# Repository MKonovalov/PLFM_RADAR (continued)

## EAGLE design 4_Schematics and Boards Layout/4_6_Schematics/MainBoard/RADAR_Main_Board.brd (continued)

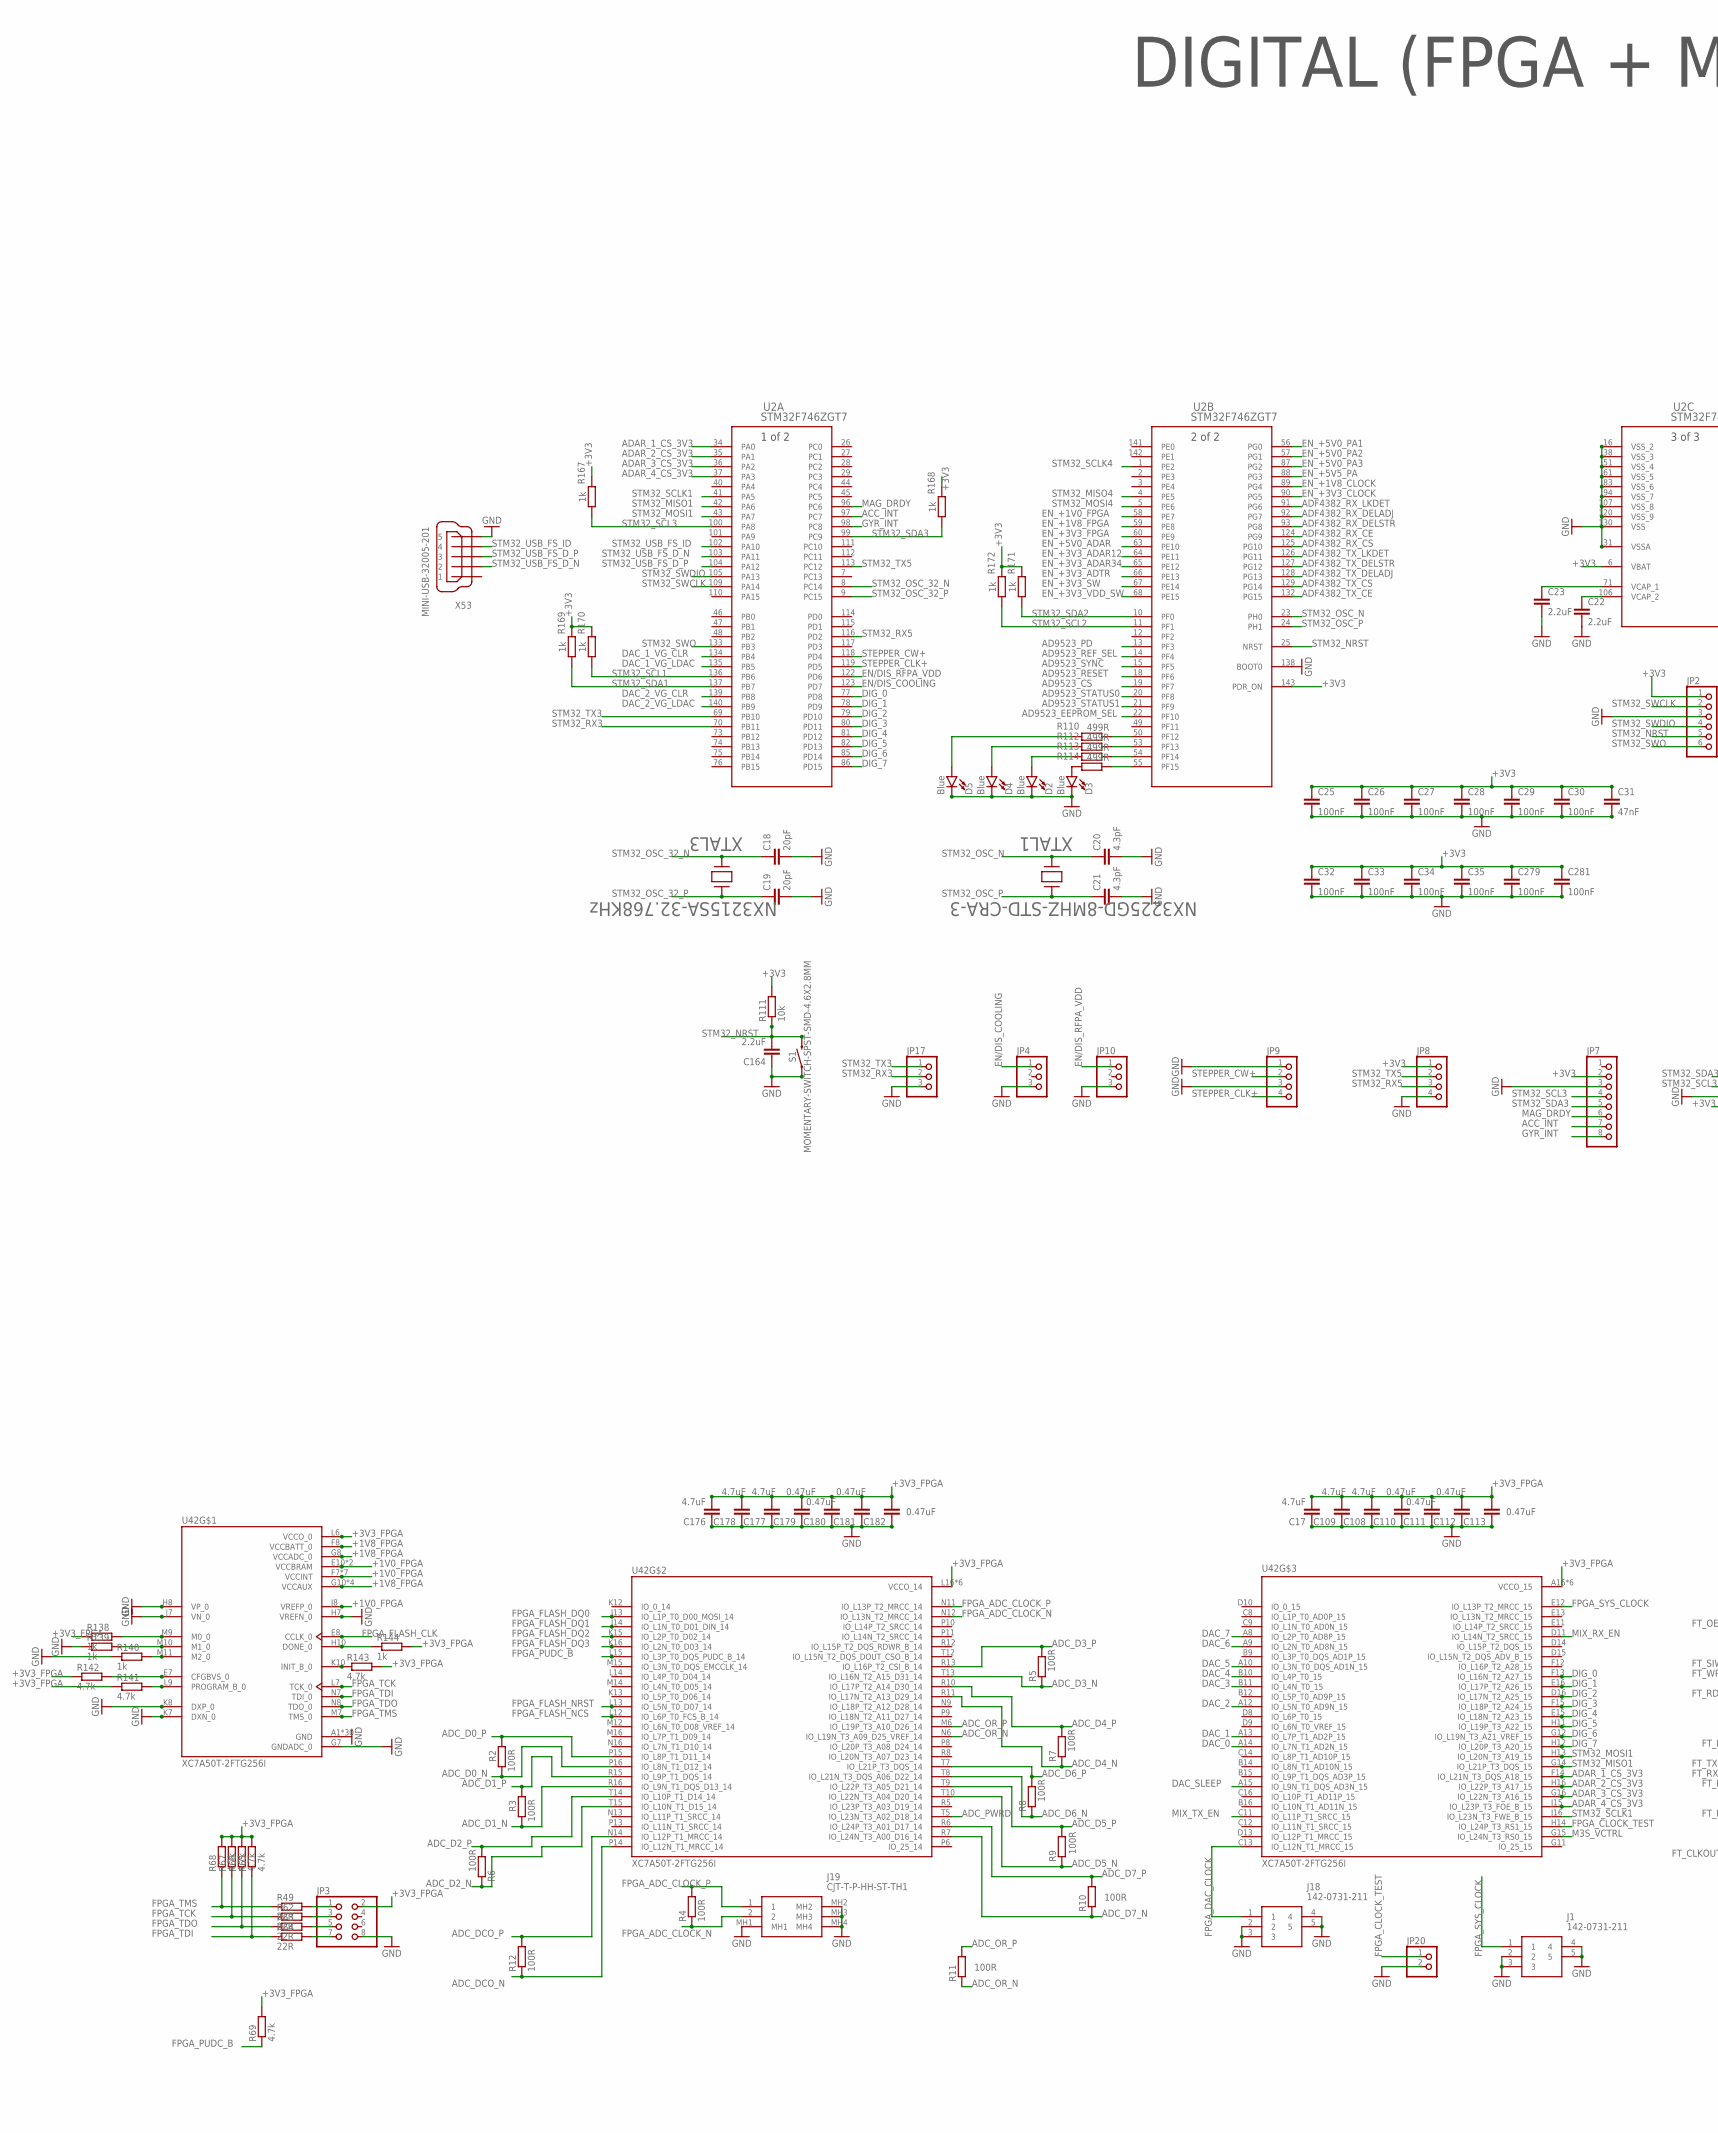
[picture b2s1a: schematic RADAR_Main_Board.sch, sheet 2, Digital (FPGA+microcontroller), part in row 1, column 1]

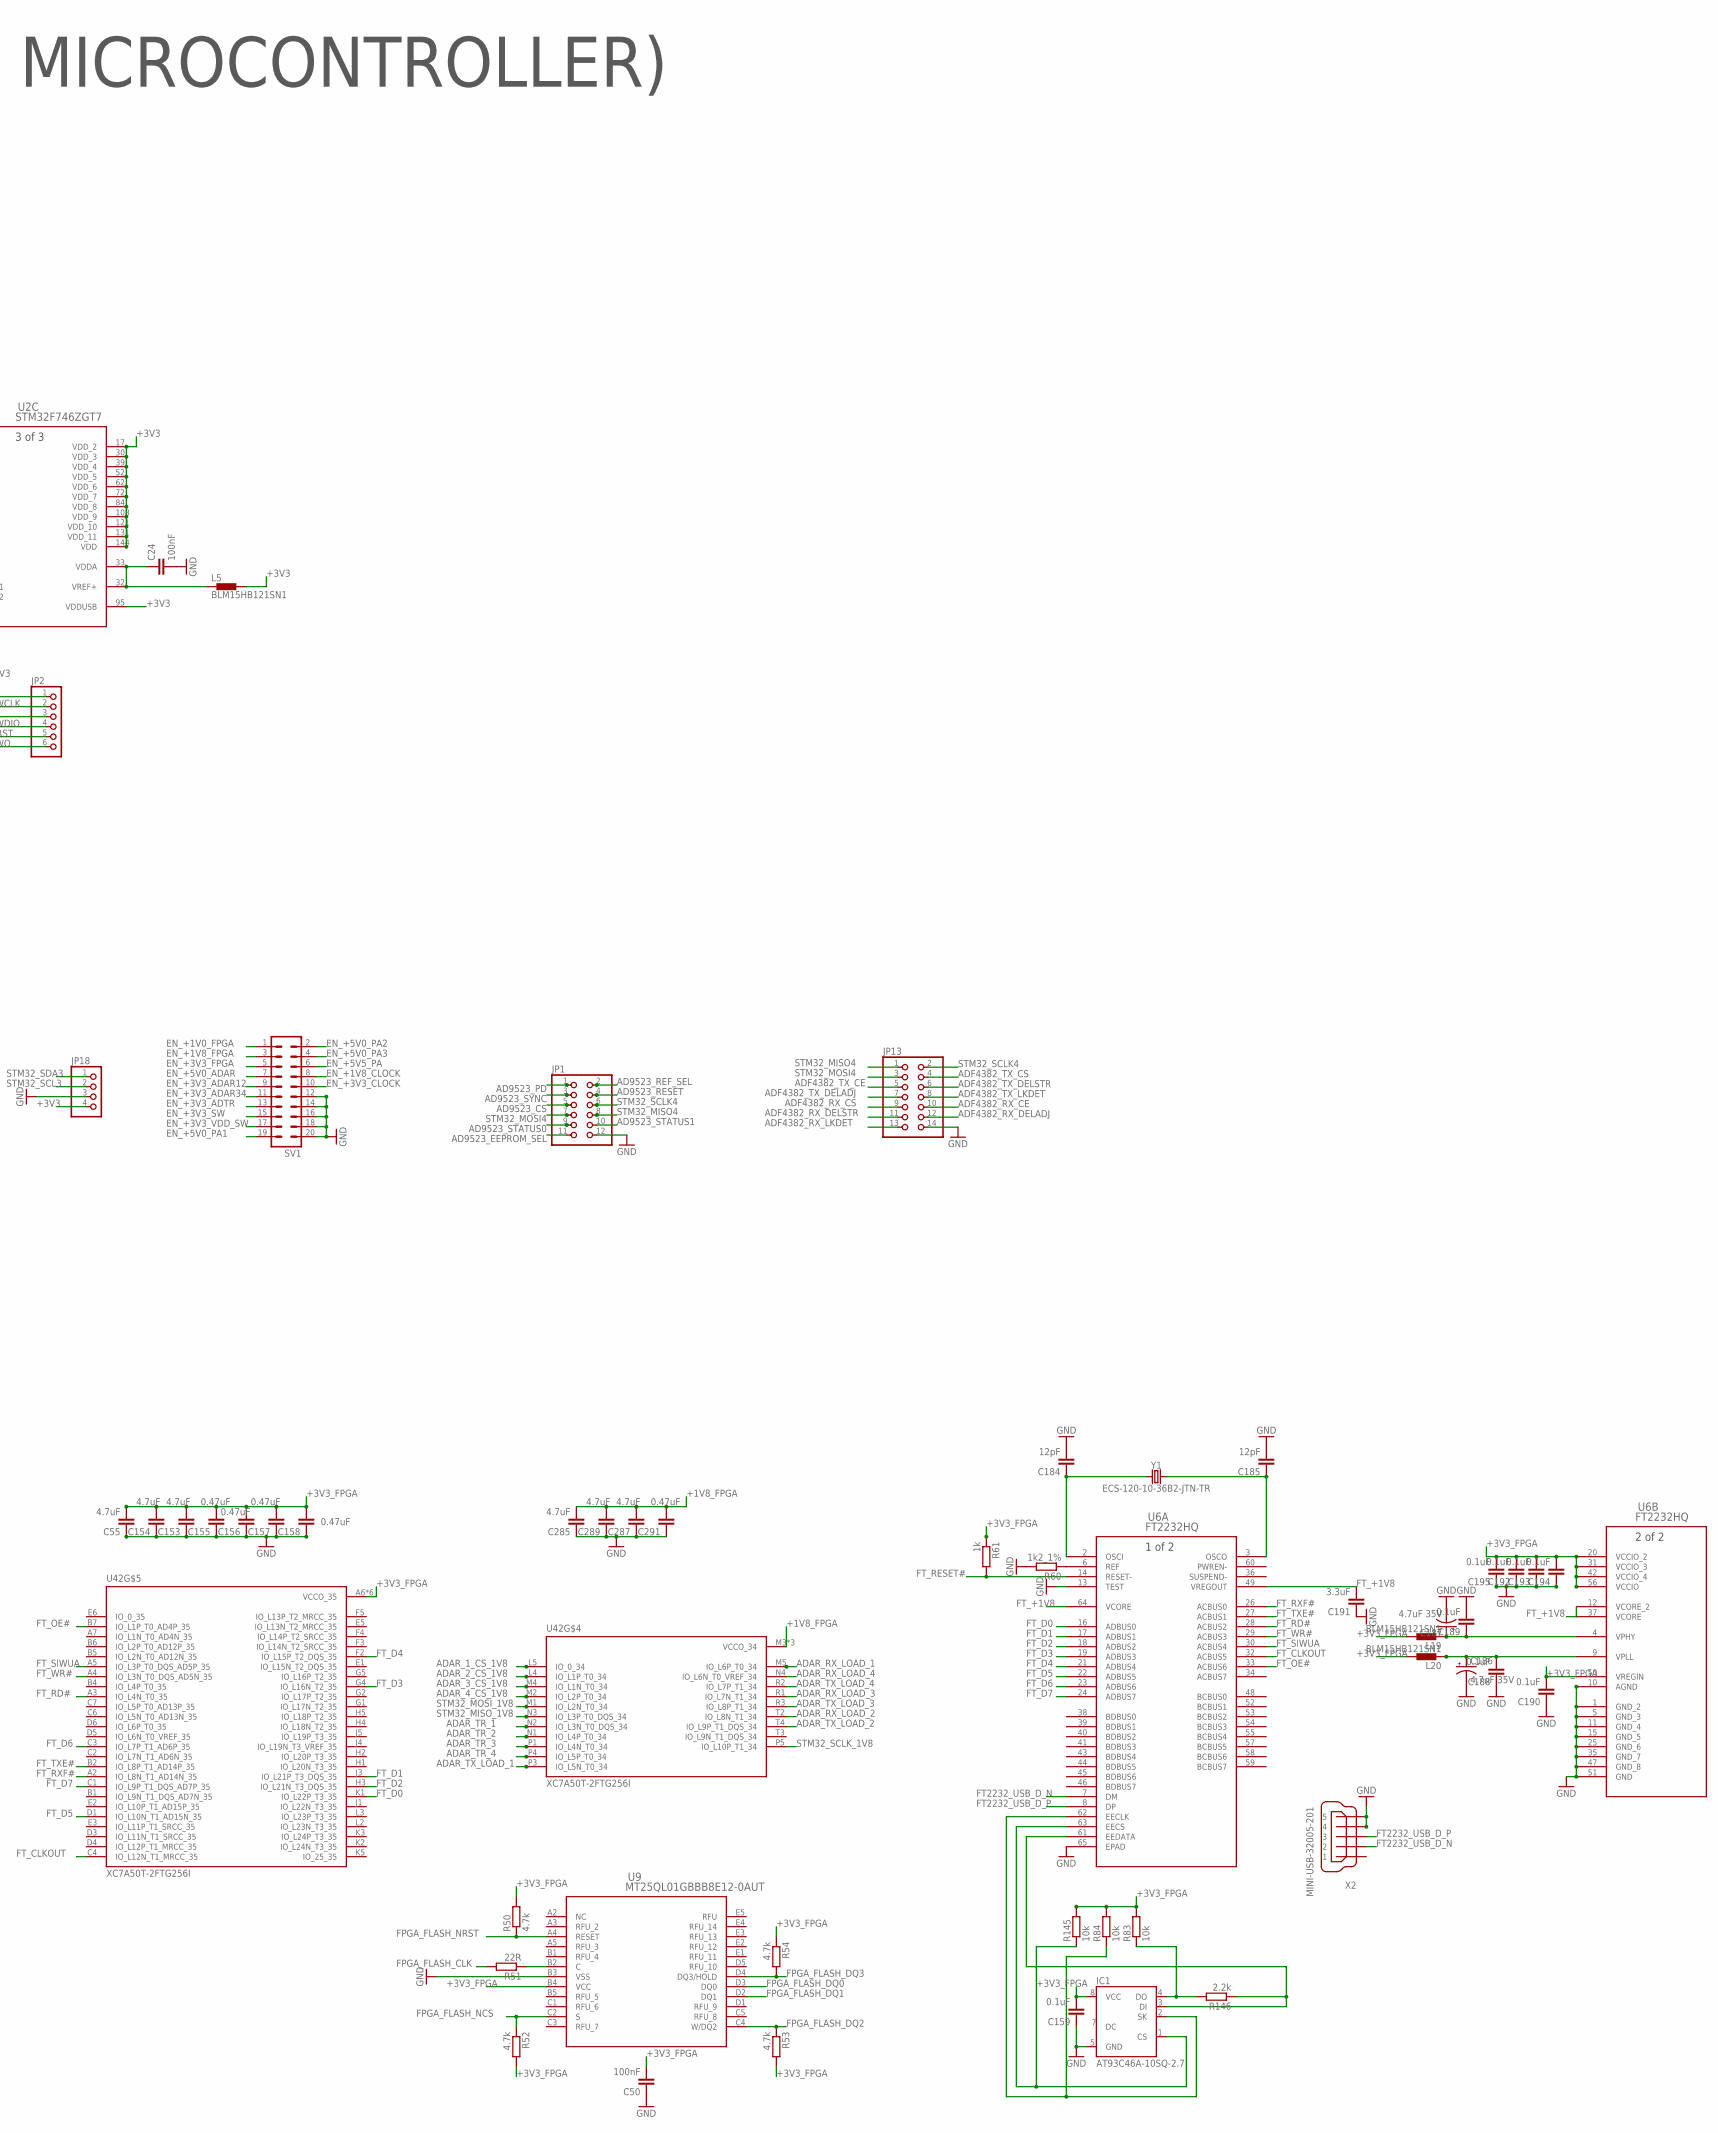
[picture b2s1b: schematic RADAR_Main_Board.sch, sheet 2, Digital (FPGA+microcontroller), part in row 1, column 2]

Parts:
C17, C55, C108, C109, C153, C154, C176, C177, C178, C285, C287, C289: 4.7uF; C0201
C18, C19: 20pF; C0201
C20, C21: 4.3pF; C0201
C22, C23, C164: 2.2uF; C0201
C24, C25, C26, C27, C28, C29, C30, C32, C33, C34, C35, C50, C279, C281: 100nF; C0201
C31: 47nF; C0201
C110, C111, C112, C113, C155, C156, C157, C158, C179, C180, C181, C182, C291: 0.47uF; C0201
C159, C188, C189, C190, C192, C193, C194, C195: 0.1uF; C0201
C184, C185: 12pF; C0201
C186, C187: 4.7uF 35V; EIA3528
C191: 3.3uF; C0201
D2, D3, D4, D5: Blue; LED-0603
IC1: AT93C46A-10SQ-2.7; SOIC8
J1, J18: 142-0731-211; 1420731211
J19: CJT-T-P-HH-ST-TH1; CJTTPHHSTTH1
JP1: PINHD-2X6; 2X06
JP2: PINHD-1X6; 1X06
JP3: PINHD-2X4; 2X04
JP4, JP10, JP17: PINHD-1X3; 1X03
JP7: PINHD-1X8; 1X08
JP8, JP9, JP18: PINHD-1X4; 1X04
JP13: PINHD-2X7; 2X07
JP20: PINHD-1X2; 1X02
L5, L19, L20: BLM15HB121SN1; 0402
R2, R3, R4, R5, R6, R7, R8, R9, R10, R11, R12: 100R; R0201
R49, R51, R62, R63, R64: 22R; R0201
R50, R52, R53, R54, R65, R66, R67, R68, R69, R141, R142, R143: 4.7k; R0201
R60: 1k2_1%; R0201
R61, R138, R139, R140, R144, R167, R168, R169, R170, R171, R172: 1k; R0201
R83, R84, R111, R145: 10k; R0201
R110, R112, R113, R114: 499R; R0201
R146: 2.2k; R0201
S1: MOMENTARY-SWITCH-SPST-SMD-4.6X2.8MM; TACTILE_SWITCH_SMD_4.6X2.8MM
SV1: MA10-2
U2: STM32F746ZGT7; LQFP-144_STM
U6: FT2232HQ; 64QFN_FT2232HQ_FTD
U9: MT25QL01GBBB8E12-0AUT; BGA24_MT25QL_MRN
U42: XC7A50T-2FTG256I; BGA256C100P16X16_1700X1700X155
X2, X53: MINI-USB-32005-201; 32005-201
XTAL1: NX3225GD-8MHZ-STD-CRA-3; XTAL_NX3225GD-8MHZ-STD-CRA-3_N
XTAL3: NX3215SA-32.768KHz; XTAL_NX3225GD-8MHZ-STD-CRA-3_N
Y1: ECS-120-10-36B2-JTN-TR; CRYSTAL-SMD-2X2.5MM

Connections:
+1V0_FPGA: U42.E10 (VCCBRAM), U42.F7 (VCCINT), U42.F9 (VCCINT), U42.F11 (VCCBRAM), U42.G6 (VCCINT), U42.H9 (VCCINT), U42.J6 (VCCINT), U42.J8 (VREFP_0), U42.K9 (VCCINT), U42.L8 (VCCINT); also elsewhere on the board
+1V8_FPGA: C285.2, C287.2, C289.2, C291.2, U42.F8 (VCCBATT_0), U42.G8 (VCCADC_0), U42.G10 (VCCAUX), U42.J10 (VCCAUX), U42.K11 (VCCAUX), U42.L10 (VCCAUX), U42.M3 (VCCO_34), U42.R4 (VCCO_34), U42.T1 (VCCO_34); also elsewhere on the board
+3V3: C25.1, C26.1, C27.1, C28.1, C29.1, C30.1, C31.1, C32.1, C33.1, C34.1, C35.1, C279.1, C281.1, JP2.1, JP7.2, JP8.1, JP18.4, L5.2, R111.2, R167.1, R168.1, R169.1, R170.1, R171.1, R172.1, U2.6 (VBAT), U2.17 (VDD_2), U2.30 (VDD_3), U2.39 (VDD_4), U2.52 (VDD_5), U2.62 (VDD_6), U2.72 (VDD_7), U2.84 (VDD_8), U2.95 (VDDUSB), U2.108 (VDD_9), U2.121 (VDD_10), U2.131 (VDD_11), U2.143 (PDR_ON), U2.144 (VDD); also elsewhere on the board
+3V3_FPGA: C17.2, C50.2, C55.2, C108.2, C109.2, C110.2, C111.2, C112.2, C113.2, C153.2, C154.2, C155.2, C156.2, C157.2, C158.2, C159.2, C176.2, C177.2, C178.2, C179.2, C180.2, C181.2, C182.2, C190.2, C192.2, C193.2, C194.2, C195.2, IC1.8 (VCC), JP3.2, L19.2, L20.2, R50.2, R52.2, R53.2, R54.1, R61.1, R65.2, R66.2, R67.2, R68.2, R69.2, R83.2, R84.2, R138.1, R141.1, R142.1, R143.2, R144.2, R145.2, U6.20 (VCCIO_2), U6.31 (VCCIO_3), U6.42 (VCCIO_4), U6.50 (VREGIN), U6.56 (VCCIO), U9.B4 (VCC), U42.A6 (VCCO_35), U42.A16 (VCCO_15), U42.B3 (VCCO_35), U42.B13 (VCCO_15), U42.C10 (VCCO_15), U42.D7 (VCCO_35), U42.E4 (VCCO_35), U42.E14 (VCCO_15), U42.F1 (VCCO_35), U42.H15 (VCCO_15), U42.J2 (VCCO_35), U42.J12 (VCCO_15), U42.L6 (VCCO_0); also elsewhere on the board
ACC_INT: JP7.7, U2.97 (PC7)
AD9523_CS: JP1.5, U2.19 (PF7)
AD9523_EEPROM_SEL: JP1.11, U2.22 (PF10)
AD9523_PD: JP1.1, U2.13 (PF3)
AD9523_REF_SEL: JP1.2, U2.14 (PF4)
AD9523_RESET: JP1.4, U2.18 (PF6)
AD9523_STATUS0: JP1.9, U2.20 (PF8)
AD9523_STATUS1: JP1.10, U2.21 (PF9)
AD9523_SYNC: JP1.3, U2.15 (PF5)
ADAR_1_CS_1V8: U42.L5 (IO_0_34); also elsewhere on the board
ADAR_1_CS_3V3: U2.34 (PA0), U42.F14 (IO_L21N_T3_DQS_A18_15)
ADAR_2_CS_1V8: U42.L4 (IO_L1P_T0_34); also elsewhere on the board
ADAR_2_CS_3V3: U2.35 (PA1), U42.H16 (IO_L22P_T3_A17_15)
ADAR_3_CS_1V8: U42.M4 (IO_L1N_T0_34); also elsewhere on the board
ADAR_3_CS_3V3: U2.36 (PA2), U42.G16 (IO_L22N_T3_A16_15)
ADAR_4_CS_1V8: U42.M2 (IO_L2P_T0_34); also elsewhere on the board
ADAR_4_CS_3V3: U2.37 (PA3), U42.J15 (IO_L23P_T3_FOE_B_15)
ADAR_RX_LOAD_1: U42.M5 (IO_L6P_T0_34); also elsewhere on the board
ADAR_RX_LOAD_2: U42.T2 (IO_L8N_T1_34); also elsewhere on the board
ADAR_RX_LOAD_3: U42.R1 (IO_L7N_T1_34); also elsewhere on the board
ADAR_RX_LOAD_4: U42.N4 (IO_L6N_T0_VREF_34); also elsewhere on the board
ADAR_TR_1: U42.N2 (IO_L3N_T0_DQS_34); also elsewhere on the board
ADAR_TR_2: U42.N1 (IO_L4P_T0_34); also elsewhere on the board
ADAR_TR_3: U42.P1 (IO_L4N_T0_34); also elsewhere on the board
ADAR_TR_4: U42.P4 (IO_L5P_T0_34); also elsewhere on the board
ADAR_TX_LOAD_1: U42.P3 (IO_L5N_T0_34); also elsewhere on the board
ADAR_TX_LOAD_2: U42.T4 (IO_L9P_T1_DQS_34); also elsewhere on the board
ADAR_TX_LOAD_3: U42.R3 (IO_L8P_T1_34); also elsewhere on the board
ADAR_TX_LOAD_4: U42.R2 (IO_L7P_T1_34); also elsewhere on the board
ADC_D0_N: R2.1, U42.P16 (IO_L8N_T1_D12_14); also elsewhere on the board
ADC_D0_P: R2.2, U42.P15 (IO_L8P_T1_D11_14); also elsewhere on the board
ADC_D1_N: R3.1, U42.R16 (IO_L9N_T1_DQS_D13_14); also elsewhere on the board
ADC_D1_P: R3.2, U42.R15 (IO_L9P_T1_DQS_14); also elsewhere on the board
ADC_D2_N: R6.1, U42.T15 (IO_L10N_T1_D15_14); also elsewhere on the board
ADC_D2_P: R6.2, U42.T14 (IO_L10P_T1_D14_14); also elsewhere on the board
ADC_D3_N: R5.1, U42.T13 (IO_L16N_T2_A15_D31_14); also elsewhere on the board
ADC_D3_P: R5.2, U42.R13 (IO_L16P_T2_CSI_B_14); also elsewhere on the board
ADC_D4_N: R7.1, U42.R11 (IO_L17N_T2_A13_D29_14); also elsewhere on the board
ADC_D4_P: R7.2, U42.R10 (IO_L17P_T2_A14_D30_14); also elsewhere on the board
ADC_D5_N: R9.1, U42.T10 (IO_L22N_T3_A04_D20_14); also elsewhere on the board
ADC_D5_P: R9.2, U42.T9 (IO_L22P_T3_A05_D21_14); also elsewhere on the board
ADC_D6_N: R8.1, U42.T8 (IO_L21N_T3_DQS_A06_D22_14); also elsewhere on the board
ADC_D6_P: R8.2, U42.T7 (IO_L21P_T3_DQS_14); also elsewhere on the board
ADC_D7_N: R10.1, U42.R7 (IO_L24N_T3_A00_D16_14); also elsewhere on the board
ADC_D7_P: R10.2, U42.R6 (IO_L24P_T3_A01_D17_14); also elsewhere on the board
ADC_DCO_N: R12.1, U42.P14 (IO_L12N_T1_MRCC_14); also elsewhere on the board
ADC_DCO_P: R12.2, U42.N14 (IO_L12P_T1_MRCC_14); also elsewhere on the board
ADC_OR_N: R11.1, U42.N6 (IO_L19N_T3_A09_D25_VREF_14); also elsewhere on the board
ADC_OR_P: R11.2, U42.M6 (IO_L19P_T3_A10_D26_14); also elsewhere on the board
ADC_PWRD: U42.T5 (IO_L23N_T3_A02_D18_14); also elsewhere on the board
ADF4382_RX_CE: JP13.10, U2.124 (PG9)
ADF4382_RX_CS: JP13.9, U2.125 (PG10)
ADF4382_RX_DELADJ: JP13.12, U2.92 (PG7)
ADF4382_RX_DELSTR: JP13.11, U2.93 (PG8)
ADF4382_RX_LKDET: JP13.13, U2.91 (PG6)
ADF4382_TX_CE: JP13.5, U2.132 (PG15)
ADF4382_TX_CS: JP13.4, U2.129 (PG14)
ADF4382_TX_DELADJ: JP13.7, U2.128 (PG13)
ADF4382_TX_DELSTR: JP13.6, U2.127 (PG12)
ADF4382_TX_LKDET: JP13.8, U2.126 (PG11)
DAC_0: U42.A14 (IO_L7N_T1_AD2N_15); also elsewhere on the board
DAC_1: U42.A13 (IO_L7P_T1_AD2P_15); also elsewhere on the board
DAC_1_VG_CLR: U2.134 (PB4); also elsewhere on the board
DAC_1_VG_LDAC: U2.135 (PB5); also elsewhere on the board
DAC_2: U42.A12 (IO_L5N_T0_AD9N_15); also elsewhere on the board
DAC_2_VG_CLR: U2.139 (PB8); also elsewhere on the board
DAC_2_VG_LDAC: U2.140 (PB9); also elsewhere on the board
DAC_3: U42.B11 (IO_L4N_T0_15); also elsewhere on the board
DAC_4: U42.B10 (IO_L4P_T0_15); also elsewhere on the board
DAC_5: U42.A10 (IO_L3N_T0_DQS_AD1N_15); also elsewhere on the board
DAC_6: U42.A9 (IO_L2N_T0_AD8N_15); also elsewhere on the board
DAC_7: U42.A8 (IO_L2P_T0_AD8P_15); also elsewhere on the board
DAC_SLEEP: U42.A15 (IO_L9N_T1_DQS_AD3N_15); also elsewhere on the board
DIG_0: U2.77 (PD8), U42.F13 (IO_L16N_T2_A27_15)
DIG_1: U2.78 (PD9), U42.E16 (IO_L17P_T2_A26_15)
DIG_2: U2.79 (PD10), U42.D16 (IO_L17N_T2_A25_15)
DIG_3: U2.80 (PD11), U42.F15 (IO_L18P_T2_A24_15)
DIG_4: U2.81 (PD12), U42.E15 (IO_L18N_T2_A23_15)
DIG_5: U2.82 (PD13), U42.H11 (IO_L19P_T3_A22_15)
DIG_6: U2.85 (PD14), U42.G12 (IO_L19N_T3_A21_VREF_15)
DIG_7: U2.86 (PD15), U42.H12 (IO_L20P_T3_A20_15)
EN/DIS_COOLING: JP4.1, U2.123 (PD7)
EN/DIS_RFPA_VDD: JP10.1, U2.122 (PD6)
EN_+1V0_FPGA: SV1.1, U2.58 (PE7)
EN_+1V8_CLOCK: SV1.8, U2.89 (PG4)
EN_+1V8_FPGA: SV1.3, U2.59 (PE8)
EN_+3V3_ADAR12: SV1.9, U2.64 (PE11)
EN_+3V3_ADAR34: SV1.11, U2.65 (PE12)
EN_+3V3_ADTR: SV1.13, U2.66 (PE13)
EN_+3V3_CLOCK: SV1.10, U2.90 (PG5)
EN_+3V3_FPGA: SV1.5, U2.60 (PE9)
EN_+3V3_SW: SV1.15, U2.67 (PE14)
EN_+3V3_VDD_SW: SV1.17, U2.68 (PE15)
EN_+5V0_ADAR: SV1.7, U2.63 (PE10)
EN_+5V0_PA1: SV1.19, U2.56 (PG0)
EN_+5V0_PA2: SV1.2, U2.57 (PG1)
EN_+5V0_PA3: SV1.4, U2.87 (PG2)
EN_+5V5_PA: SV1.6, U2.88 (PG3)
FPGA_ADC_CLOCK_N: J19.2, R4.1, U42.N12 (IO_L13N_T2_MRCC_14)
FPGA_ADC_CLOCK_P: J19.1, R4.2, U42.N11 (IO_L13P_T2_MRCC_14)
FPGA_CLOCK_TEST: JP20.1, U42.H14 (IO_L24P_T3_RS1_15)
FPGA_DAC_CLOCK: J18.1, U42.C13 (IO_L12N_T1_MRCC_15)
FPGA_DONE: R144.1, U2.44 (PC4), U42.H10 (DONE_0)
FPGA_FLASH_CLK: R51.2, U42.E8 (CCLK_0)
FPGA_FLASH_DQ0: U42.J13 (IO_L1P_T0_D00_MOSI_14); also elsewhere on the board
FPGA_FLASH_DQ1: U42.J14 (IO_L1N_T0_D01_DIN_14); also elsewhere on the board
FPGA_FLASH_DQ2: R53.1, U42.K15 (IO_L2P_T0_D02_14); also elsewhere on the board
FPGA_FLASH_DQ3: R54.2, U42.K16 (IO_L2N_T0_D03_14); also elsewhere on the board
FPGA_FLASH_NCS: R52.1, U42.L12 (IO_L6P_T0_FCS_B_14); also elsewhere on the board
FPGA_FLASH_NRST: R50.1, U42.L13 (IO_L5N_T0_D07_14); also elsewhere on the board
FPGA_PUDC_B: R69.1, U42.L15 (IO_L3P_T0_DQS_PUDC_B_14)
FPGA_SYS_CLOCK: J1.1, U42.E12 (IO_L13P_T2_MRCC_15)
FPGA_TCK: R62.1, R67.1, U42.L7 (TCK_0)
FPGA_TDI: R64.1, R65.1, U42.N7 (TDI_0)
FPGA_TDO: R63.1, R66.1, U42.N8 (TDO_0)
FPGA_TMS: R49.1, R68.1, U42.M7 (TMS_0)
FT2232_USB_D_N: U6.7 (DM), X2.2
FT2232_USB_D_P: U6.8 (DP), X2.3
FT_+1V8: C191.2, U6.12 (VCORE_2), U6.37 (VCORE), U6.49 (VREGOUT), U6.64 (VCORE)
FT_CLKOUT: U6.32 (ACBUS5), U42.C4 (IO_L12N_T1_MRCC_35)
FT_D0: U6.16 (ADBUS0), U42.K1 (IO_L22P_T3_35)
FT_D1: U6.17 (ADBUS1), U42.J3 (IO_L21P_T3_DQS_35)
FT_D2: U6.18 (ADBUS2), U42.H3 (IO_L21N_T3_DQS_35)
FT_D3: U6.19 (ADBUS3), U42.G4 (IO_L16N_T2_35)
FT_D4: U6.21 (ADBUS4), U42.F2 (IO_L15P_T2_DQS_35)
FT_D5: U6.22 (ADBUS5), U42.D1 (IO_L10N_T1_AD15N_35)
FT_D6: U6.23 (ADBUS6), U42.C3 (IO_L7P_T1_AD6P_35)
FT_D7: U6.24 (ADBUS7), U42.C1 (IO_L9P_T1_DQS_AD7P_35)
FT_OE#: U6.33 (ACBUS6), U42.B7 (IO_L1P_T0_AD4P_35)
FT_RD#: U6.28 (ACBUS2), U42.A3 (IO_L4N_T0_35)
FT_RESET#: R61.2, U6.14 (RESET-)
FT_RXF#: U6.26 (ACBUS0), U42.A2 (IO_L8N_T1_AD14N_35)
FT_SIWUA: U6.30 (ACBUS4), U42.A5 (IO_L3P_T0_DQS_AD5P_35)
FT_TXE#: U6.27 (ACBUS1), U42.B2 (IO_L8P_T1_AD14P_35)
FT_WR#: U6.29 (ACBUS3), U42.A4 (IO_L3N_T0_DQS_AD5N_35)
GYR_INT: JP7.8, U2.98 (PC8)
M3S_VCTRL: U42.G15 (IO_L24N_T3_RS0_15); also elsewhere on the board
MAG_DRDY: JP7.6, U2.96 (PC6)
MIX_RX_EN: U42.D11 (IO_L14N_T2_SRCC_15); also elsewhere on the board
MIX_TX_EN: U42.C11 (IO_L11P_T1_SRCC_15); also elsewhere on the board
unnamed: C23.1, U2.71 (VCAP_1)
unnamed: C22.1, U2.106 (VCAP_2)
unnamed: C24.1, L5.1, U2.32 (VREF+), U2.33 (VDDA)
unnamed: R51.1, U9.B2 (C)
unnamed: JP3.1, R49.2
unnamed: JP3.3, R62.2
unnamed: JP3.5, R63.2
unnamed: JP3.7, R64.2
unnamed: R110.2, U2.50 (PF12)
unnamed: IC1.4 (DO), R83.1, R146.2
unnamed: R112.2, U2.53 (PF13)
unnamed: D3.A, R114.1
unnamed: R113.2, U2.54 (PF14)
unnamed: R114.2, U2.55 (PF15)
unnamed: D2.A, R113.1
unnamed: D4.A, R112.1
unnamed: D5.A, R110.1
unnamed: R138.2, U42.M9 (M0_0)
unnamed: R139.2, U42.M10 (M1_0)
unnamed: R140.2, U42.M11 (M2_0)
unnamed: R141.2, U42.L9 (PROGRAM_B_0)
unnamed: R142.2, U42.E7 (CFGBVS_0)
unnamed: R143.1, U42.K10 (INIT_B_0)
unnamed: R60.1, U6.6 (REF)
unnamed: C184.1, U6.2 (OSCI), Y1.P1 (1)
unnamed: C185.1, U6.3 (OSCO), Y1.P3 (2)
unnamed: C186.A (+), C188.2, L20.1, U6.9 (VPLL)
unnamed: C187.A (+), C189.1, L19.1, U6.4 (VPHY)
unnamed: IC1.1 (CS), R145.1, U6.63 (EECS)
unnamed: IC1.2 (SK), R84.1, U6.62 (EECLK)
unnamed: IC1.3 (DI), R146.1, U6.61 (EEDATA)
STEPPER_CLK+: JP9.4, U2.119 (PD5)
STEPPER_CW+: JP9.2, U2.118 (PD4)
STM32_MISO1: U2.42 (PA6), U42.G14 (IO_L21P_T3_DQS_15)
STM32_MISO4: JP1.8, JP13.1, U2.4 (PE5)
STM32_MISO_1V8: U42.N3 (IO_L3P_T0_DQS_34); also elsewhere on the board
STM32_MOSI1: U2.43 (PA7), U42.H13 (IO_L20N_T3_A19_15)
STM32_MOSI4: JP1.7, JP13.3, U2.5 (PE6)
STM32_MOSI_1V8: U42.M1 (IO_L2N_T0_34); also elsewhere on the board
STM32_NRST: C164.2, JP2.5, R111.1, S1.3 (2), S1.4 (2), U2.25 (NRST)
STM32_OSC_32_N: C18.1, U2.8 (PC14), XTAL3.2
STM32_OSC_32_P: C19.1, U2.9 (PC15), XTAL3.1
STM32_OSC_N: C20.1, U2.23 (PH0), XTAL1.2
STM32_OSC_P: C21.1, U2.24 (PH1), XTAL1.1
STM32_RX3: JP17.2, U2.70 (PB11)
STM32_RX5: JP8.3, U2.116 (PD2)
STM32_SCL1: R170.2, U2.136 (PB6); also elsewhere on the board
STM32_SCL2: R172.2, U2.11 (PF1); also elsewhere on the board
STM32_SCL3: JP7.4, JP18.2, R167.2, U2.100 (PA8)
STM32_SCLK1: U2.41 (PA5), U42.J16 (IO_L23N_T3_FWE_B_15)
STM32_SCLK4: JP1.6, JP13.2, U2.1 (PE2)
STM32_SCLK_1V8: U42.P5 (IO_L10P_T1_34); also elsewhere on the board
STM32_SDA1: R169.2, U2.137 (PB7); also elsewhere on the board
STM32_SDA2: R171.2, U2.10 (PF0); also elsewhere on the board
STM32_SDA3: JP7.5, JP18.1, R168.2, U2.99 (PC9)
STM32_SWCLK: JP2.2, U2.109 (PA14)
STM32_SWDIO: JP2.4, U2.105 (PA13)
STM32_SWO: JP2.6, U2.133 (PB3)
STM32_TX3: JP17.1, U2.69 (PB10)
STM32_TX5: JP8.2, U2.113 (PC12)
STM32_USB_FS_D_N: U2.103 (PA11), X53.2
STM32_USB_FS_D_P: U2.104 (PA12), X53.3
STM32_USB_FS_ID: U2.102 (PA10), X53.4

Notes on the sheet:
DIGITAL (FPGA + MICROCONTROLLER)

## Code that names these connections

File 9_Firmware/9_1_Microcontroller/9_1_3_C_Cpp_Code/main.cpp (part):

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};

/* ---- rail-good monitoring (RAIL_FAULT.h) -----------------------------------
 * Three regulators report PG on the power board, each on its own connector to PC0/PC1/PC2.
 * The pins are read with internal pull-downs, so an open harness reads LOW and is reported
 * as a fault rather than silently as "good".
 */
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static RailFault_Monitor_t g_rails;

/* ---- strobe acknowledgement (STROBE_ACK.h) ---------------------------------
 * The FPGA answers on PC3: a request clears the line, consumption sets it.  We score each
 * request *before* issuing the next one, because the FPGA clears the line as soon as it sees
 * the new request - checking afterwards would always read low.
 */
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static bool     g_ack_path_ok;

/* The FPGA's configuration status (issue #13).  The main board carries FPGA_DONE from the FPGA's
 * DONE_0/INIT_B_0 to U2.PC4, so the MCU can see a failed or partial configuration - which it
 * could not before, when the pins terminated in pull resistors only. */
static FpgaConfig_t g_fpga_cfg;
static bool         g_fpga_cfg_reported;
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 * The ADC's CSB used to be tied to a rail - which the datasheet names as the way to disable the
 * SPI - SCLK/DFS sat on solder jumper SJ1, and SDIO was unconnected.  The pins are
 * DRVDD-referenced 1.8 V logic (absolute maximum 2.0 V), so they reach the MCU through U92, a
 * TXS0104E translator; PC10 = CSB, PC11 = SCLK, PC13 = SDIO.
 */
static uint8_t g_adc_ovr_config;   /* read back at bring-up: 0x01 on a healthy part */
static bool    g_adc_spi_ok;

static void adc_spi_csb(bool level)  { HAL_GPIO_WritePin(GPIOC, GPIO_PIN_10, level ? GPIO_PIN_SET : GPIO_PIN_RESET); }
static void adc_spi_sclk(bool level) { HAL_GPIO_WritePin(GPIOC, GPIO_PIN_11, level ? GPIO_PIN_SET : GPIO_PIN_RESET); }
static void adc_spi_sdio_out(bool level) { HAL_GPIO_WritePin(GPIOC, GPIO_PIN_13, level ? GPIO_PIN_SET : GPIO_PIN_RESET); }

static void adc_spi_sdio_dir(bool output)
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 *
 * The edges must be counted by an interrupt: one pulse is 1 us high with a
 * 3 us period, all within ~21 us of the frame start, which the per-frame main
 * loop cannot sample.  To enable: configure PD15 (FPGA_DIG7_Pin) as a
 * rising-edge EXTI input and register agcPulseCounter.onEdge() through the
 * project's IRQ layer (no_os_irq_ctrl_init + no_os_irq_register_callback, as
 * stm32_gpio_irq.c does for other pins).
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};

// Convenience HAL wrappers for AD9523 control pins (GPIOF as you said)
static inline void AD9523_PD(bool v)        { HAL_GPIO_WritePin(GPIOF, AD9523_PD_Pin, v ? GPIO_PIN_SET : GPIO_PIN_RESET); }
static inline void AD9523_REF_SEL(bool v)   { HAL_GPIO_WritePin(GPIOF, AD9523_REF_SEL_Pin, v ? GPIO_PIN_SET : GPIO_PIN_RESET); }
static inline void AD9523_SYNC_PULSE(void)  { HAL_GPIO_WritePin(GPIOF, AD9523_SYNC_Pin, GPIO_PIN_SET); HAL_Delay(1); HAL_GPIO_WritePin(GPIOF, AD9523_SYNC_Pin, GPIO_PIN_RESET); }
static inline void AD9523_RESET_ASSERT()    { HAL_GPIO_WritePin(GPIOF, AD9523_RESET_Pin, GPIO_PIN_RESET); } // check polarity
static inline void AD9523_RESET_RELEASE()   { HAL_GPIO_WritePin(GPIOF, AD9523_RESET_Pin, GPIO_PIN_SET); }
static inline void AD9523_CS(bool v)        { HAL_GPIO_WritePin(GPIOF, AD9523_CS_Pin, v ? GPIO_PIN_SET : GPIO_PIN_RESET); }
static inline void AD9523_EEPROM_SEL(bool v){ HAL_GPIO_WritePin(GPIOF, AD9523_EEPROM_SEL_Pin, v ? GPIO_PIN_SET : GPIO_PIN_RESET); }

/* USER CODE END PV */

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    HAL_Delay(10);

    // Step 2: Disable PA power supplies
    DIAG("PWR", "Step 2: Disable PA 5V supplies (EN_P_5V0_PA1/PA2/PA3 LOW)");
    HAL_GPIO_WritePin(EN_P_5V0_PA1_GPIO_Port, EN_P_5V0_PA1_Pin | EN_P_5V0_PA2_Pin | EN_P_5V0_PA3_Pin, GPIO_PIN_RESET);
    HAL_Delay(10);

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    // 1. Check AD9523 Clock Generator
    static uint32_t last_clock_check = 0;
    if (HAL_GetTick() - last_clock_check > 5000) {
        GPIO_PinState s0 = HAL_GPIO_ReadPin(AD9523_STATUS0_GPIO_Port, AD9523_STATUS0_Pin);
        GPIO_PinState s1 = HAL_GPIO_ReadPin(AD9523_STATUS1_GPIO_Port, AD9523_STATUS1_Pin);
        DIAG_GPIO("CLK", "AD9523 STATUS0", s0);
        DIAG_GPIO("CLK", "AD9523 STATUS1", s1);
        if (s0 == GPIO_PIN_RESET || s1 == GPIO_PIN_RESET) {
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    DIAG_ERR("PA", "Applying PA bias sequence (gate off -> drain off)");
    (void)PA_BiasSequence_Apply(&g_pa_bias_io, &g_pa_bias_params, false);

    DIAG_ERR("PA", "Cutting PA 5V supplies (PA1/PA2/PA3 LOW)");
    HAL_GPIO_WritePin(EN_P_5V0_PA1_GPIO_Port, EN_P_5V0_PA1_Pin, GPIO_PIN_RESET);
    HAL_GPIO_WritePin(EN_P_5V0_PA2_GPIO_Port, EN_P_5V0_PA2_Pin, GPIO_PIN_RESET);
    HAL_GPIO_WritePin(EN_P_5V0_PA3_GPIO_Port, EN_P_5V0_PA3_Pin, GPIO_PIN_RESET);
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
  DIAG_SECTION("AD9523 POWER SEQUENCING");
  DIAG("PWR", "Asserting AD9523 reset (pin LOW)");
  HAL_GPIO_WritePin(AD9523_RESET_GPIO_Port,AD9523_RESET_Pin,GPIO_PIN_RESET);

  //Power sequencing AD9523
  DIAG("PWR", "Enabling 1.8V clock rail");
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  HAL_GPIO_WritePin(EN_P_3V3_CLOCK_GPIO_Port,EN_P_3V3_CLOCK_Pin,GPIO_PIN_SET);
  HAL_Delay(100);
  DIAG("PWR", "Releasing AD9523 reset (pin HIGH)");
  HAL_GPIO_WritePin(AD9523_RESET_GPIO_Port,AD9523_RESET_Pin,GPIO_PIN_SET);
  HAL_Delay(100);
  DIAG("PWR", "AD9523 power sequencing complete -- all rails up, reset released");

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
  // check if there is a lock via direct GPIO (independent of register read above)
  DIAG("LO", "Direct GPIO lock detect pins:");
  DIAG_GPIO("LO", "ADF4382_TX_LKDET", ADF4382_TX_LKDET_GPIO_Port, ADF4382_TX_LKDET_Pin);
  DIAG_GPIO("LO", "ADF4382_RX_LKDET", ADF4382_RX_LKDET_GPIO_Port, ADF4382_RX_LKDET_Pin);
  if(HAL_GPIO_ReadPin (ADF4382_TX_LKDET_GPIO_Port, ADF4382_TX_LKDET_Pin))
  {
      // Set The LED_1 ON!
      HAL_GPIO_WritePin(LED_1_GPIO_Port, LED_1_Pin, GPIO_PIN_SET);
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      DIAG_WARN("LO", "TX NOT locked via GPIO -- LED_1 OFF");
  }

  if(HAL_GPIO_ReadPin (ADF4382_RX_LKDET_GPIO_Port, ADF4382_RX_LKDET_Pin))
  {
      // Set The LED_2 ON!
      HAL_GPIO_WritePin(LED_2_GPIO_Port, LED_2_Pin, GPIO_PIN_SET);
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	  /* DAC1: Address 0b1001000 = 0x48 */
	  DIAG("PA", "Initializing DAC1 (I2C1, addr=0x48, 8-bit)");
	  if (!DAC5578_Init(&hdac1, &hi2c1, 0x48, 8,
			  DAC_1_VG_LDAC_GPIO_Port, DAC_1_VG_LDAC_Pin,
			  DAC_1_VG_CLR_GPIO_Port, DAC_1_VG_CLR_Pin)) {
		  DIAG_ERR("PA", "DAC1 init FAILED -- calling Error_Handler()");
		  Error_Handler();
	  }
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	  /* DAC2: Address 0b1001001 = 0x49 */
	  DIAG("PA", "Initializing DAC2 (I2C1, addr=0x49, 8-bit)");
	  if (!DAC5578_Init(&hdac2, &hi2c1, 0x49, 8,
			  DAC_2_VG_LDAC_GPIO_Port, DAC_2_VG_LDAC_Pin,
			  DAC_2_VG_CLR_GPIO_Port, DAC_2_VG_CLR_Pin)) {
		  DIAG_ERR("PA", "DAC2 init FAILED -- calling Error_Handler()");
		  Error_Handler();
	  }
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
	  /* Optional: Use hardware LDAC for simultaneous update of all channels */
	  DIAG("PA", "Pulsing LDAC on both DACs for simultaneous update");
	  HAL_GPIO_WritePin(DAC_1_VG_LDAC_GPIO_Port, DAC_1_VG_LDAC_Pin, GPIO_PIN_RESET);
	  HAL_GPIO_WritePin(DAC_2_VG_LDAC_GPIO_Port, DAC_2_VG_LDAC_Pin, GPIO_PIN_RESET);
	  HAL_Delay(1);
	  HAL_GPIO_WritePin(DAC_1_VG_LDAC_GPIO_Port, DAC_1_VG_LDAC_Pin, GPIO_PIN_SET);
	  HAL_GPIO_WritePin(DAC_2_VG_LDAC_GPIO_Port, DAC_2_VG_LDAC_Pin, GPIO_PIN_SET);

	  /* Bring the array up in the documented order (gate off -> drain -> operating bias)
	   * through the tested sequence rather than by hand.  Duty-cycling the array -- the
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              DIAG_ERR("LO", "Lock LOST in main loop! TX=%s RX=%s",
                       tx_locked ? "LOCKED" : "UNLOCKED",
                       rx_locked ? "LOCKED" : "UNLOCKED");
              DIAG_GPIO("LO", "TX_LKDET (direct)", ADF4382_TX_LKDET_GPIO_Port, ADF4382_TX_LKDET_Pin);
              DIAG_GPIO("LO", "RX_LKDET (direct)", ADF4382_RX_LKDET_GPIO_Port, ADF4382_RX_LKDET_Pin);
          } else {
              DIAG("LO", "Lock poll OK: TX=LOCKED RX=LOCKED");
          }
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
      runRadarPulseSequence();

      /* [AGC] Outer-loop AGC: sync enable from FPGA via DIG_6 (PD14),
       * then read saturation flag (DIG_5 / PD13) and adjust ADAR1000 VGA
       * common gain once per radar frame (~258 ms).
       * FPGA register host_agc_enable is the single source of truth —
       * DIG_6 propagates it to MCU every frame.
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      if (outerAgc.enabled) {
          bool sat = HAL_GPIO_ReadPin(FPGA_DIG5_SAT_GPIO_Port,
                                      FPGA_DIG5_SAT_Pin) == GPIO_PIN_SET;
          /* [FIX WP4.2] DIG_7 (PD15) is a pulse train now, not a level: do
           * not read it with HAL_GPIO_ReadPin.  consume() returns the severity
           * class the FPGA sent (1..7), 0 when no pulses arrived, or
           * AgcPulseCounter::kUnknown when the line produced more edges than the
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  __HAL_RCC_GPIOD_CLK_ENABLE();

  /*Configure GPIO pin Output Level */
  HAL_GPIO_WritePin(GPIOF, AD9523_PD_Pin|AD9523_REF_SEL_Pin|AD9523_SYNC_Pin|AD9523_RESET_Pin
                          |AD9523_CS_Pin|AD9523_EEPROM_SEL_Pin|LED_1_Pin|LED_2_Pin
                          |LED_3_Pin|LED_4_Pin, GPIO_PIN_RESET);

  /*Configure GPIO pin Output Level */
  HAL_GPIO_WritePin(GPIOA, ADAR_1_CS_3V3_Pin|ADAR_2_CS_3V3_Pin|ADAR_3_CS_3V3_Pin|ADAR_4_CS_3V3_Pin, GPIO_PIN_RESET);

  /*Configure GPIO pin Output Level */
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
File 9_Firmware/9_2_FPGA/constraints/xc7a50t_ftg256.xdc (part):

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# CLOCK CONSTRAINTS
# ============================================================================

# 100MHz System Clock (AD9523 OUT6 → FPGA_SYS_CLOCK → Bank 15 MRCC pin E12)
set_property PACKAGE_PIN E12 [get_ports {clk_100m}]
set_property IOSTANDARD LVCMOS33 [get_ports {clk_100m}]
create_clock -name clk_100m -period 10.0 [get_ports {clk_100m}]
set_input_jitter [get_clocks clk_100m] 0.1

# 120MHz DAC Clock (AD9523 OUT11 → FPGA_DAC_CLOCK → Bank 15 MRCC pin D13)
# NOTE: The physical DAC (U3, AD9708) receives its clock directly from the
#       AD9523 via a separate net (DAC_CLOCK), NOT from the FPGA. The FPGA
#       uses this clock input for internal DAC data timing only. The RTL port
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# banks. IBUFDS input buffers are VCCO-independent — they work correctly even
# with VCCO=3.3V. The BIVC-1 DRC (voltage conflict with LVCMOS33 adc_pwdn)
# is waived in the build script since this bank has only LVDS *inputs*.
set_property PACKAGE_PIN N14 [get_ports {adc_dco_p}]
set_property PACKAGE_PIN P14 [get_ports {adc_dco_n}]
set_property IOSTANDARD LVDS_25 [get_ports {adc_dco_p}]
set_property IOSTANDARD LVDS_25 [get_ports {adc_dco_n}]
set_property DIFF_TERM TRUE [get_ports {adc_dco_p}]
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# (Place 30-876). The schematic routes CLKOUT to C4; this cannot be
# changed without a board respin. The clock still uses an IBUFG and
# reaches the clock network — the constraint only disables the DRC check.
set_property PACKAGE_PIN C4 [get_ports {ft_clkout}]
set_property IOSTANDARD LVCMOS33 [get_ports {ft_clkout}]
create_clock -name ft_clkout -period 16.667 [get_ports {ft_clkout}]
set_input_jitter [get_clocks ft_clkout] 0.2
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# ============================================================================
# RESET (Active-Low)
# ============================================================================
# DIG_4 (STM32 PD12 → FPGA Bank 15 pin E15)
# STM32 firmware uses HAL_GPIO_WritePin to assert/deassert FPGA reset.

set_property PACKAGE_PIN E15 [get_ports {reset_n}]
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# set_property SLEW FAST [get_ports {dac_clk}]

# DAC Sleep Control — DAC_SLEEP net
set_property PACKAGE_PIN A15 [get_ports {dac_sleep}]
set_property IOSTANDARD LVCMOS33 [get_ports {dac_sleep}]

# RF Switch Control — M3S_VCTRL net
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# ============================================================================

# ADAR1000 TX Load Pins (via level shifters, active-high pulse)
set_property PACKAGE_PIN P3 [get_ports {adar_tx_load_1}]
set_property PACKAGE_PIN T4 [get_ports {adar_tx_load_2}]
set_property PACKAGE_PIN R3 [get_ports {adar_tx_load_3}]
set_property PACKAGE_PIN R2 [get_ports {adar_tx_load_4}]

# ADAR1000 RX Load Pins
set_property PACKAGE_PIN M5 [get_ports {adar_rx_load_1}]
set_property PACKAGE_PIN T2 [get_ports {adar_rx_load_2}]
set_property PACKAGE_PIN R1 [get_ports {adar_rx_load_3}]
set_property PACKAGE_PIN N4 [get_ports {adar_rx_load_4}]

# Bank 34 VCCO = 1.8V → must use LVCMOS18 (not LVCMOS33)
set_property IOSTANDARD LVCMOS18 [get_ports {adar_*_load_*}]

# ADAR1000 TR (Transmit/Receive) Pins
set_property PACKAGE_PIN N2 [get_ports {adar_tr_1}]
set_property PACKAGE_PIN N1 [get_ports {adar_tr_2}]
set_property PACKAGE_PIN P1 [get_ports {adar_tr_3}]
set_property PACKAGE_PIN P4 [get_ports {adar_tr_4}]
set_property IOSTANDARD LVCMOS18 [get_ports {adar_tr_*}]

# ============================================================================
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set_property IOSTANDARD LVCMOS33 [get_ports {stm32_*_3v3}]

# 1.8V Side (to ADAR1000, Bank 34, VCCO=1.8V)
set_property PACKAGE_PIN P5 [get_ports {stm32_sclk_1v8}]
set_property PACKAGE_PIN M1 [get_ports {stm32_mosi_1v8}]
set_property PACKAGE_PIN N3 [get_ports {stm32_miso_1v8}]
set_property PACKAGE_PIN L5 [get_ports {stm32_cs_adar1_1v8}]
set_property PACKAGE_PIN L4 [get_ports {stm32_cs_adar2_1v8}]
set_property PACKAGE_PIN M4 [get_ports {stm32_cs_adar3_1v8}]
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# ============================================================================
# STM32 CONTROL INTERFACE (DIG bus, Bank 15, VCCO=3.3V)
# ============================================================================
# DIG_0..DIG_4 are STM32 outputs (PD8-PD12) → FPGA inputs
# DIG_5..DIG_7 are STM32 inputs (PD13-PD15) ← FPGA outputs (all three used)

set_property PACKAGE_PIN F13 [get_ports {stm32_new_chirp}]

# Issue #13: the strobe acknowledgement the MCU polls (free bank-15 pin, same bank and
# standard as the strobe it answers, so no level shift is involved)
set_property PACKAGE_PIN B16 [get_ports {fpga_strobe_ack}]
set_property IOSTANDARD LVCMOS33 [get_ports {fpga_strobe_ack}]
set_property PACKAGE_PIN E16 [get_ports {stm32_new_elevation}]   ;# DIG_1 (PD9)
set_property PACKAGE_PIN D16 [get_ports {stm32_new_azimuth}]     ;# DIG_2 (PD10)
set_property PACKAGE_PIN F15 [get_ports {stm32_mixers_enable}]   ;# DIG_3 (PD11)
set_property IOSTANDARD LVCMOS33 [get_ports {stm32_new_*}]
set_property IOSTANDARD LVCMOS33 [get_ports {stm32_mixers_enable}]
# reset_n is DIG_4 (PD12) — constrained above in the RESET section

# ADC out-of-range flag (AD9484 OR) — bank 14, LVDS_25 like the data lanes.
# Ball numbers come from the board file's FPGA symbol: it maps
# IO_L19P_T3_A10_D26_14 -> M6 and IO_L19N_T3_A09_D25_VREF_14 -> N6
# (same method verified against adc_pwdn, pad T5).
# Not consumed by the RTL until this commit; now it drives DIG_5/DIG_7.
set_property PACKAGE_PIN M6 [get_ports {adc_or_p}]
set_property PACKAGE_PIN N6 [get_ports {adc_or_n}]
set_property IOSTANDARD LVDS_25 [get_ports {adc_or_p}]
set_property IOSTANDARD LVDS_25 [get_ports {adc_or_n}]
set_property DIFF_TERM TRUE [get_ports {adc_or_p}]

# DIG_5 = H11, DIG_6 = G12, DIG_7 = H12 — FPGA→STM32 status outputs
# DIG_5: AGC saturation flag (PD13 on STM32)
# DIG_6: AGC enable mirror (PD14)
# DIG_7: AGC hard-overload flag, |sat_count| >= 8 (PD15)
# DIG_6: AGC enable flag (PD14) — mirrors FPGA host_agc_enable to STM32
# DIG_7: AGC hard-overload flag (PD15)
set_property PACKAGE_PIN H11 [get_ports {gpio_dig5}]
set_property PACKAGE_PIN G12 [get_ports {gpio_dig6}]
set_property PACKAGE_PIN H12 [get_ports {gpio_dig7}]
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set_property DRIVE 8 [get_ports {ft_siwu}]
set_property DRIVE 8 [get_ports {ft_data[*]}]

# ft_clkout constrained above in CLOCK CONSTRAINTS section (C4, 60 MHz)

# --------------------------------------------------------------------------
# FT2232H Source-Synchronous Timing Constraints
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# ============================================================================
# The following RTL output ports have no corresponding FPGA pins in the
# schematic. The only FPGA→STM32 outputs available are DIG_5 (H11),
# DIG_6 (G12), and DIG_7 (H12) — only 3 pins for potentially 60+ signals.
#
# These constraints are commented out. If status readback is needed, either:
#   (a) Multiplex selected status bits onto DIG_5/6/7, or
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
